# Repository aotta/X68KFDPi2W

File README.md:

# X68KFDPi2W
X68KFDPi2W - Floppies drive emulator All-In-One for Sharp X68000

The design is an evolution of my previous X68KFDPico, and allows the two drives of the X68000 to be emulated both externally and internally connected. The engine of the emulator are two Raspberry Pico, one ‘normal’ to handle the special floppy signals and the other ‘W’ to emulate the floppies, SDcard image management and a simple web server to choose the disks to be inserted in the floppies.
Ejection and insertion of the disks can be done via the two keys in the X68KFDPi2W or by connecting the cables of the original floppy keys (in case they are not present internally). The same for the internal LEDs, which are however replicated in the emulator (only the green one, the red LED is managed only for the internal one).
Floppies images format supported:

| Format | Extension | Read | Write | Notes |
|---|---|---|---|---|
| Raw sector image | `.HDM`, `.XDF` | yes | yes | X68000 2HD 1232KB (77x2x8x1024); 2HC 1.2MB (80x2x15x512) also recognised by size |
| D88 | `.D88`, `.D68`, `.88D` | yes | yes | 2HD media, any sector layout (sector sizes, numbering, deleted data). The write protect flag of the image is honoured |
| DIM (DIFC.X) | `.DIM` | yes | yes | 2HD, 2HS, 2HC, 2HDE, 26x256. 2HQ (1.44MB) is not supported (needs a 300rpm drive) |
| HFE | `.HFE` | yes | no | the drive reports write protect |

Writing to floppy images is supported: the X68000 can copy files, format disks (FORMAT) and save games to the images on the SD card.
2D/2DD (double density) images and FM sectors are not supported.

### How writing works

- WRDATA is captured by a PIO state machine that measures the time between flux transitions, and a DMA channel stores them in RAM, so no write is missed while the Pico is busy (WiFi, web server).
- Core 1, which generates the read flux, watches WRGATE and records drive, side, track and the position on the track where each write starts. A normal sector write has no ID field, so the sector is found from that position; when formatting, the ID fields written by the X68000 are used.
- Core 0 decodes the MFM data with the routines of the Adafruit Floppy library (`mfm_impl.h`), checks the CRC, updates the track in memory (a verify read returns the new data immediately) and saves the sectors to the SD card when the write session ends (step, side or drive change, or 100ms without writes).
- Track format: a whole track is longer than the capture buffer, so the sectors not captured are filled with the same fill byte used by the X68000 (log line `format: 5 sectors decoded, 3 filled with E5`).
- The serial log shows one `WR:` line per write and per save.

### Web interface

- Live status of the two drives (activity/write LED, track, R/W or read only, image format), updated every second.
- One click insert in drive 0 or 1 for every image in the folder; folders are listed first.
- "Make default" stores the full path of the image in `wifi.cfg`; on an empty drive it makes the drive start empty at power on (★ DEFAULT tag).
- "New disk": creates a blank, unformatted 2HD 1232KB image (`.HDM` or `.D88`) in the current folder; insert it and format it on the X68000 with FORMAT.

### Options (top of X68KFDPi2W.ino)

- `DEBUG_BUS` (default 0): 1 prints MOTOR / DRIVE SELECT changes on the serial port (verbose).
- `RESET_ON_DESELECT` (default 1): the head goes back to track 0 when the drive is deselected or the motor stops. Needed by games that ask to swap disks (e.g. A-JAX).
- `BUS_ON_INSERTED` (default 0): READY and the bus outputs (74LVC245) are active only while an emulated drive is in use (motor on and drive selected), as in the 03/2025 release. With 1 they follow the disk inserted signals, and some games (e.g. Dracula) hang after loading Human68k.
- `READY_FOLLOWS_MOTOR`, `DF_EN_PULLDOWN`, `TRK0_FOLLOWS_SELECT` (default 0): experimental behaviours, off.
- `READY_PULSE_ON_INSERT` (default 1): when a disk is inserted (button), READY goes low for `READY_PULSE_MS` (50 ms). The FDC sees a READY change, as with a real drive; needed by games that wait for the new disk after an eject (e.g. Valis II).

### Eject / insert controller (X68kfdPico1_11, plain Pico)

The second Pico handles the X68000 OPTION_SEL protocol (eject, lock, LED blink, disk in drive, interrupt). Version 1.10:

- The protocol runs on core 1 in a tight loop and answers an OPTION_SEL access in about 0.2 µs; buttons, LEDs and the serial log run on core 0.
- /DISK_IN_DRIVE reports the drive addressed by the last OPTION_SEL and goes HIGH (no disk) as soon as a drive that is not ours is addressed (before, drives 2/3 looked inserted).
- /INT is asserted at every disk change (eject by the X68000, button) and cleared by the next access to that drive; if it is not served it is pulsed again every 100 ms.
- The eject is ignored when the lock signal is active in the same access; buttons count only when held 30 ms.
- Options at the top of the sketch: `FORCE_DRIVE01` (1 = always drives 0/1, 0 = read the INTEXT jumper), `DIAG` (1 = print the OPTION_SEL accesses every second), `EJECT_DELAY_MS`, `INT_REPEAT_MS`, `INT_GAP_US`, `BUTTON_MS`.
- Board: "Raspberry Pi Pico".

Valis II (original Japanese version): after the intro the game ejects disk A and waits, without any message, for the next disk (Disk D) in drive 0. Load it in drive 0 from the web page and press the insert button of drive 0.

### Building the firmware

- Arduino IDE with the Raspberry Pi Pico core by Earle Philhower (tested with 6.3.x), board "Raspberry Pi Pico W".
- Libraries: Adafruit Floppy (and its dependency Adafruit BusIO); SdFat is the one included with the core.
- `drive.pio.h` is generated from `drive.pio` with `pioasm drive.pio drive.pio.h` (the Arduino IDE does not do it).
- `logo.h` contains the web page logo (from `vari/logo.png`).

A special thanks to Adafruit team for their great "Floppy library", from wich i starded for floppy emulation part.

**NOTE** Last revision fix a conflicts found when using both an internal and an external X68KFDPi2W for 4 floppy emulation, now disabled 74LVC245 when drives not enabled. 
Please use last PCB, X68KFDPico.u2f and X68KFDPi2W.u2f version!!

**NOTE 2** Some games need tricks to properly boot, for example A-JAX works when starting with both drive off (leds off). When using 2HDboot.x for launching games from HD, you must "insert" floppy 1 & 2 pushing buttons when 2hdboot starts, then "eject" pushing again button after few seconds.

You need to add a "wifi.cfg" in root of your SDcard, with this 4 text row:
SSID
WIFI PASSWORD
Default floppy in drive 0
Default floppy in drive 1

The 2 lines related to the default floppys can be omitted and changed everytime via Web server (a full path, e.g. `/games/boot.hdm`, or an empty line for an empty drive).

Gerbers file are provided for the PCB, add you pico clone, and flash the firmware ".uf2" in the Pico and in the Pico W by connecting it while pressing button on Pico and drop it in the opened windows on PC.

For any comments or questions about the projects, please use the official thread in the forum: https://nfggames.com/forum2/index.php?topic=7512.0

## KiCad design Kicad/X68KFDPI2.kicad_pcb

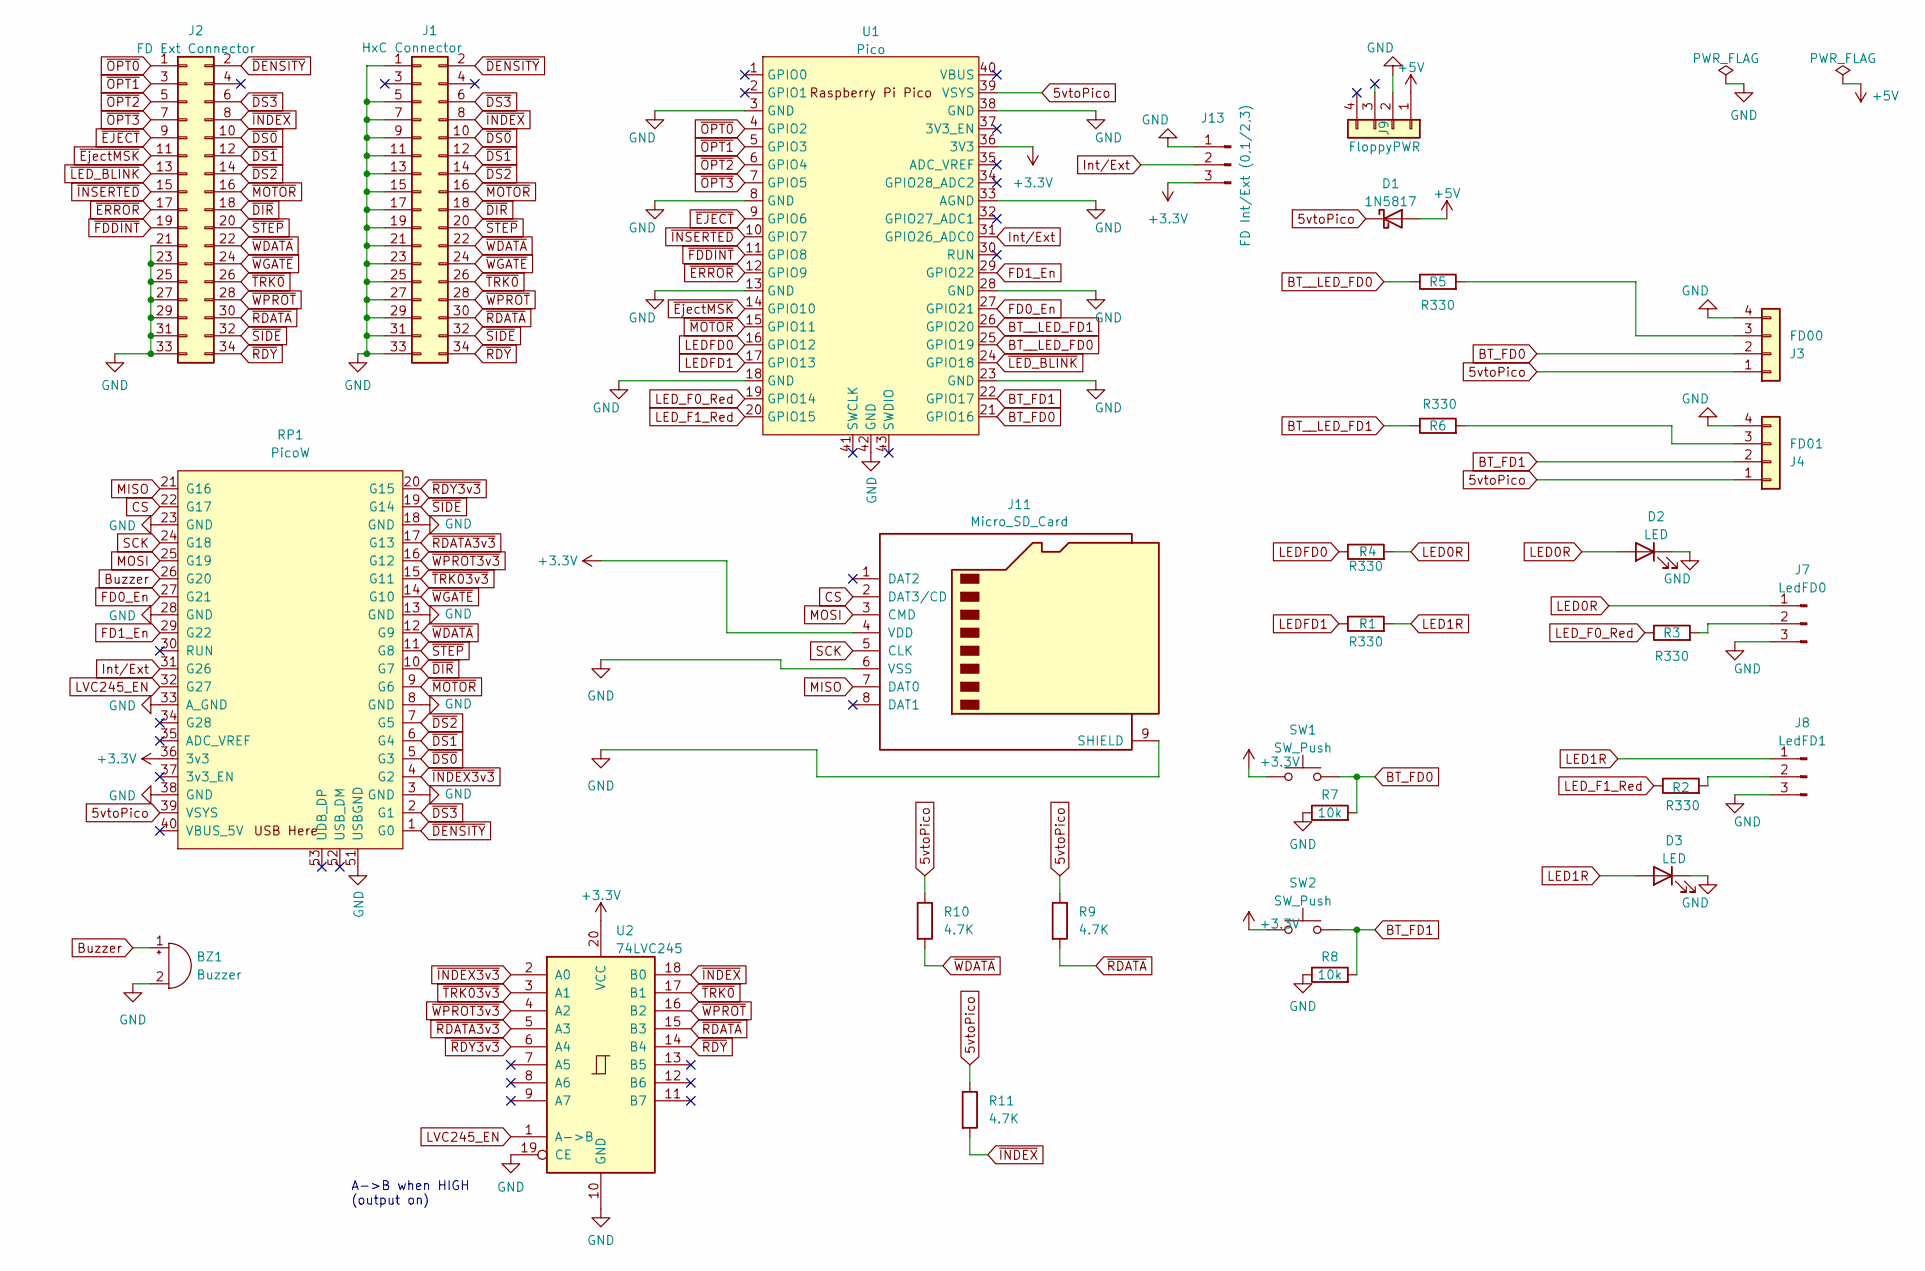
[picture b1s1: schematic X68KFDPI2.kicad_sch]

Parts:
BZ1: Buzzer; Buzzer_12x9.5RM7.6
D1: 1N5817; D_DO-15_P12.70mm_Horizontal
D2, D3: LED; LED_D3.0mm
J1: HxC Connector; IDC-Header_2x17_P2.54mm_Horizontal
J2: FD Ext Connector; IDC-Header_2x17_P2.54mm_Horizontal
J3: FD00; JST_PH_B4B-PH-K_1x04_P2.00mm_Vertical
J4: FD01; JST_PH_B4B-PH-K_1x04_P2.00mm_Vertical
J7: LedFD0; JST_PH_B3B-PH-K_1x03_P2.00mm_Vertical
J8: LedFD1; JST_PH_B3B-PH-K_1x03_P2.00mm_Vertical
J9: FloppyPWR; PinHeader_1x04_P2.54mm_Horizontal
J11: Micro_SD_Card; J_SD_Card-micro_socket_A
J13: FD Int/Ext (0,1/2,3); PinHeader_1x03_P2.54mm_Vertical
R1, R2, R3, R4, R5, R6: R330; R_Axial_DIN0207_L6.3mm_D2.5mm_P10.16mm_Horizontal
R7, R8: 10k; R_Axial_DIN0207_L6.3mm_D2.5mm_P7.62mm_Horizontal
R9, R10, R11: 4.7K; R_Axial_DIN0207_L6.3mm_D2.5mm_P7.62mm_Horizontal
RP1: PicoW; Raspberry_Pi_PicoW_SMT_THT
SW1, SW2: SW_Push; SW_Tactile_SPST_Angled_PTS645Vx83-2LFS
U1: Pico; Raspberry_Pi_PicoW_SMT_THT
U2: 74LVC245; DIP-20_W7.62mm_Socket

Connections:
5vtoPico: D1.1 (K), J3.1, J4.1, R9.1, R10.1, R11.1, RP1.39 (VSYS), U1.39 (VSYS)
+3.3V: J11.4 (VDD), J13.3, RP1.36 (3v3), SW1.1, SW2.1, U1.36 (3V3), U2.20 (VCC)
+5V: D1.2 (A), J9.1
BT_FD0: J3.2, R7.2, SW1.2, U1.21 (GPIO16)
BT_FD1: J4.2, R8.2, SW2.2, U1.22 (GPIO17)
BT__LED_FD0: R5.1, U1.25 (GPIO19)
BT__LED_FD1: R6.1, U1.26 (GPIO20)
Buzzer: BZ1.1 (+), RP1.26 (G20)
CS: J11.2 (DAT3/CD), RP1.22 (G17)
FD0_En: RP1.27 (G21), U1.27 (GPIO21)
FD1_En: RP1.29 (G22), U1.29 (GPIO22)
GND: BZ1.2 (-), D2.1 (K), D3.1 (K), J1.1, J1.5, J1.7, J1.9, J1.11, J1.13, J1.15, J1.17, J1.19, J1.21, J1.23, J1.25, J1.27, J1.29, J1.31, J1.33, J2.21, J2.23, J2.25, J2.27, J2.29, J2.31, J2.33, J3.4, J4.4, J7.3, J8.3, J9.2, J11.6 (VSS), J11.9 (SHIELD), J13.1, R7.1, R8.1, RP1.3 (GND), RP1.8 (GND), RP1.13 (GND), RP1.18 (GND), RP1.23 (GND), RP1.28 (GND), RP1.33 (A_GND), RP1.38 (GND), RP1.51 (USBGND), U1.3 (GND), U1.8 (GND), U1.13 (GND), U1.18 (GND), U1.23 (GND), U1.28 (GND), U1.33 (AGND), U1.38 (GND), U1.42 (GND), U2.10 (GND), U2.19 (CE)
Int/Ext: J13.2, RP1.31 (G26), U1.31 (GPIO26_ADC0)
LED0R: D2.2 (A), J7.1, R4.2
LED1R: D3.2 (A), J8.1, R1.2
LEDFD0: R4.1, U1.16 (GPIO12)
LEDFD1: R1.1, U1.17 (GPIO13)
LED_F0_Red: R3.1, U1.19 (GPIO14)
LED_F1_Red: R2.1, U1.20 (GPIO15)
LVC245_EN: RP1.32 (G27), U2.1 (A->B)
MISO: J11.7 (DAT0), RP1.21 (G16)
MOSI: J11.3 (CMD), RP1.25 (G19)
unnamed: J3.3, R5.2
unnamed: J4.3, R6.2
unnamed: J7.2, R3.2
unnamed: J8.2, R2.2
SCK: J11.5 (CLK), RP1.24 (G18)
~DENSITY: J1.2, J2.2, RP1.1 (G0)
~DIR: J1.18, J2.18, RP1.10 (G7)
~DS0: J1.10, J2.10, RP1.5 (G3)
~DS1: J1.12, J2.12, RP1.6 (G4)
~DS2: J1.14, J2.14, RP1.7 (G5)
~DS3: J1.6, J2.6, RP1.2 (G1)
~EJECT: J2.9, U1.9 (GPIO6)
~ERROR: J2.17, U1.12 (GPIO9)
~EjectMSK: J2.11, U1.14 (GPIO10)
~FDDINT: J2.19, U1.11 (GPIO8)
~INDEX3v3: RP1.4 (G2), U2.2 (A0)
~INDEX: J1.8, J2.8, R11.2, U2.18 (B0)
~INSERTED: J2.15, U1.10 (GPIO7)
~LED_BLINK: J2.13, U1.24 (GPIO18)
~MOTOR: J1.16, J2.16, RP1.9 (G6), U1.15 (GPIO11)
~OPT0: J2.1, U1.4 (GPIO2)
~OPT1: J2.3, U1.5 (GPIO3)
~OPT2: J2.5, U1.6 (GPIO4)
~OPT3: J2.7, U1.7 (GPIO5)
~RDATA3v3: RP1.17 (G13), U2.5 (A3)
~RDATA: J1.30, J2.30, R9.2, U2.15 (B3)
~RDY3v3: RP1.20 (G15), U2.6 (A4)
~RDY: J1.34, J2.34, U2.14 (B4)
~SIDE: J1.32, J2.32, RP1.19 (G14)
~STEP: J1.20, J2.20, RP1.11 (G8)
~TRK0: J1.26, J2.26, U2.17 (B1)
~TRK03v3: RP1.15 (G11), U2.3 (A1)
~WDATA: J1.22, J2.22, R10.2, RP1.12 (G9)
~WGATE: J1.24, J2.24, RP1.14 (G10)
~WPROT3v3: RP1.16 (G12), U2.4 (A2)
~WPROT: J1.28, J2.28, U2.16 (B2)

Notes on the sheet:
A->B when HIGH (output on)

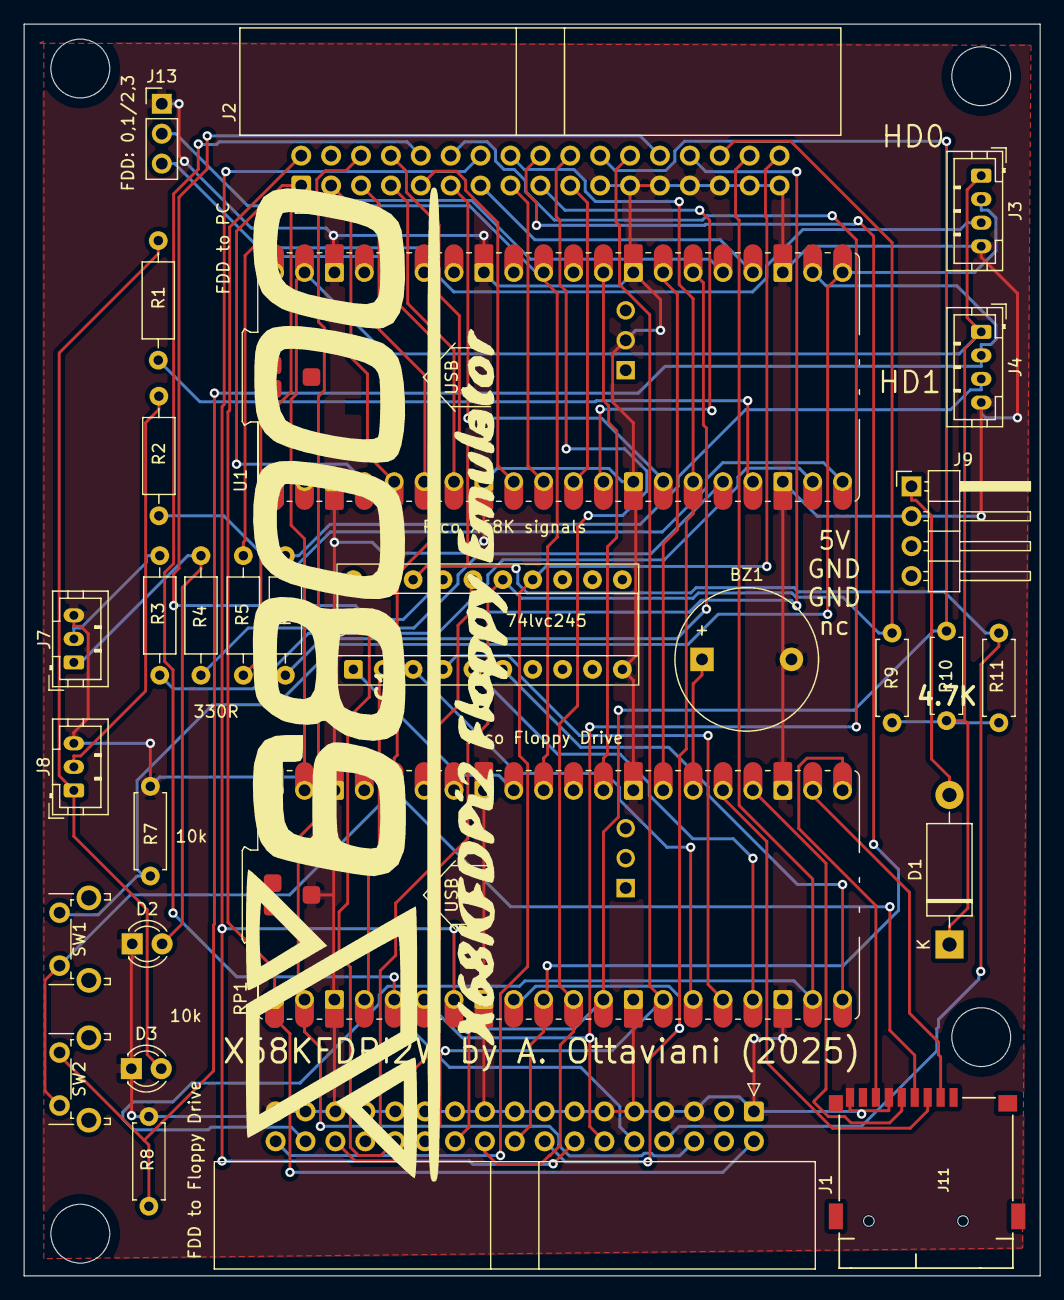
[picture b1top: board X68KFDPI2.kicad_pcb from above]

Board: 2 copper layers, 86.3 x 106.4 mm, 31 parts (1 on the bottom side), 58 nets.

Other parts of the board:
G1: LOGO; X68Klogo
Gback: LOGO; X68Klogo

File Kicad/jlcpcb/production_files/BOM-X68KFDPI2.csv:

Comment,Designator,Footprint,LCSC,Quantity
Pico,U1,Raspberry_Pi_PicoW_SMT_THT,,1
PicoW,RP1,Raspberry_Pi_PicoW_SMT_THT,,1
LedFD0,J7,JST_PH_B3B-PH-K_1x03_P2.00mm_Vertical,,1
R330,R2,R_Axial_DIN0207_L6.3mm_D2.5mm_P10.16mm_Horizontal,,1
10k,R7,R_Axial_DIN0207_L6.3mm_D2.5mm_P7.62mm_Horizontal,,1
R330,R5,R_Axial_DIN0207_L6.3mm_D2.5mm_P10.16mm_Horizontal,,1
FD01,J4,JST_PH_B4B-PH-K_1x04_P2.00mm_Vertical,,1
FloppyPWR,J9,PinHeader_1x04_P2.54mm_Horizontal,,1
R330,R1,R_Axial_DIN0207_L6.3mm_D2.5mm_P10.16mm_Horizontal,,1
74LVC245,U2,DIP-20_W7.62mm_Socket,,1
10k,R8,R_Axial_DIN0207_L6.3mm_D2.5mm_P7.62mm_Horizontal,,1
R330,R4,R_Axial_DIN0207_L6.3mm_D2.5mm_P10.16mm_Horizontal,,1
R330,R3,R_Axial_DIN0207_L6.3mm_D2.5mm_P10.16mm_Horizontal,,1
4.7K,R9,R_Axial_DIN0207_L6.3mm_D2.5mm_P7.62mm_Horizontal,,1
HxC Connector,J1,IDC-Header_2x17_P2.54mm_Horizontal,,1
4.7K,R10,R_Axial_DIN0207_L6.3mm_D2.5mm_P7.62mm_Horizontal,,1
4.7K,R11,R_Axial_DIN0207_L6.3mm_D2.5mm_P7.62mm_Horizontal,,1
"FD Int/Ext (0,1/2,3)",J13,PinHeader_1x03_P2.54mm_Vertical,,1
LED,D3,LED_D3.0mm,,1
1N5817,D1,D_DO-15_P12.70mm_Horizontal,,1
FD Ext Connector,J2,IDC-Header_2x17_P2.54mm_Horizontal,,1
SW_Push,SW1,SW_Tactile_SPST_Angled_PTS645Vx83-2LFS,,1
LedFD1,J8,JST_PH_B3B-PH-K_1x03_P2.00mm_Vertical,,1
Buzzer,BZ1,Buzzer_12x9.5RM7.6,,1
Micro_SD_Card,J11,J_SD_Card-micro_socket_A,,1
SW_Push,SW2,SW_Tactile_SPST_Angled_PTS645Vx83-2LFS,,1
FD00,J3,JST_PH_B4B-PH-K_1x04_P2.00mm_Vertical,,1
LED,D2,LED_D3.0mm,,1
R330,R6,R_Axial_DIN0207_L6.3mm_D2.5mm_P10.16mm_Horizontal,,1

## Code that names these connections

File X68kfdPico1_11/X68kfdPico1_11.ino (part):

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// 1 = always drives 0/1 (ignore the INTEXT jumper), 0 = read the jumper
// Like a real drive: after the eject command the disk takes a while to leave
// the drive, then /INT is asserted until the next access to that drive.
#define EJECT_DELAY_MS 0   // 0 = "no disk" right after the eject command (A-Jax checks it at once)
#define INT_MIN_MS 0      // 0 = cleared by the first access, like a real drive
#define INT_REPEAT_MS 100  // /INT not served: new falling edge every INT_REPEAT_MS
#define INT_GAP_US 200     // ... after releasing the line for INT_GAP_US
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#define FORCE_DRIVE01 0

//Cablage
#define OPT0                2  // Set D2 as OPT0 Read strobe
#define OPT1                3  // Set D3 as OPT1 Read strobe
#define OPT2                4  // Set D4 as OPT2 Read strobe
#define OPT3                5  // Set D5 as OPT3 Read strobe
#define Eject               6  // Set D6 as Eject Read strobe
#define Inserted            7  // Set D7 as Inserted Read strobe
#define FDDINT              8  // Set D8 as FD Interrupt Read strobe
#define Error               9  // Set D9 as Error Read strobe
#define EjectMSK           10  // Set D10 as EjectMSK Read strobe
#define Motor              11  // Set D11 as Motor Read strobe
#define LEDFD0             12  // Set D12 as LED FD0 output (Green LED)
#define LEDFD1             13  // Set D13 as LED FD1 output (Green LED)
#define LED_FD0_RED        14  // Set D14 as LED FD0 output (Red LED)
#define LED_FD1_RED        15  // Set D15 as LED FD1 output (Red LED)
#define BT_FD0             16  // Set D16 as Button FD0 Read strobe
#define BT_FD1             17  // Set D17 as Button FD1 Read strobe
#define LED_BLINK          18  // Set A0 as LED (Blink) output
#define BT_FD0_INT         19  // Set D19 as Button FD0 Read strobe from internal floppy
#define BT_FD1_INT         20  // Set D20 as Button FD1 Read strobe from internal floppy
#define DF0_EN             21  // "disk in drive 0" to the Pico W
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uint optPin[2];

void setup() {
  pinMode(OPT0, INPUT_PULLUP);
  pinMode(OPT1, INPUT_PULLUP);
  pinMode(OPT2, INPUT_PULLUP);
  pinMode(OPT3, INPUT_PULLUP);
  pinMode(Eject, INPUT_PULLUP);
  pinMode(BT_FD0, INPUT);
  pinMode(BT_FD1, INPUT);
  pinMode(LED_BLINK, INPUT_PULLUP); // Blink
  pinMode(EjectMSK, INPUT_PULLUP);  // LOCK
  pinMode(Motor, INPUT_PULLUP);
  digitalWrite(Inserted, HIGH); pinMode(Inserted, OUTPUT);
  digitalWrite(Error, HIGH);    pinMode(Error, OUTPUT);
  digitalWrite(FDDINT, HIGH);   pinMode(FDDINT, OUTPUT);
  pinMode(LEDFD0, OUTPUT);
  pinMode(LEDFD1, OUTPUT);
  pinMode(LED_FD0_RED, OUTPUT);
  pinMode(LED_FD1_RED, OUTPUT);
  pinMode(BT_FD0_INT, OUTPUT);
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#else
  bool d01 = digitalRead(INTEXT);
#endif
  optPin[0] = d01 ? OPT0 : OPT2;
  optPin[1] = d01 ? OPT1 : OPT3;
  core1_ready = true;
}

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
void __attribute__((optimize("O2"))) __not_in_flash_func(loop1)() {
  const uint32_t mA = 1u << optPin[0], mB = 1u << optPin[1];
  const uint32_t mOpt = (1u << OPT0) | (1u << OPT1) | (1u << OPT2) | (1u << OPT3);
  const uint32_t mOther = mOpt & ~(mA | mB);
  const uint32_t mEj = 1u << Eject, mLk = 1u << EjectMSK, mBl = 1u << LED_BLINK;
  const uint32_t mIns = 1u << Inserted, mInt = 1u << FDDINT;
  int who = -1;                       // drive addressed by the last strobe, -1 = not ours
  bool d[2] = {disk[0], disk[1]};
  bool intp[2] = {false, false};      // interrupt pending per drive
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  static bool prev_disk[2] = {false, false}, prev_lock[2] = {false, false}, prev_blink[2] = {false, false};
  static uint32_t prev_ej[2] = {0, 0};
  static bool started = false;
  const int btn[2] = {BT_FD0, BT_FD1};
  const int green[2] = {LEDFD0, LEDFD1}, red[2] = {LED_FD0_RED, LED_FD1_RED};
  const int intout[2] = {BT_FD0_INT, BT_FD1_INT}, en[2] = {DF0_EN, DF1_EN};
  uint32_t now = millis();

  if (!started && now > 2000) {
    started = true;
    Serial.printf("X68kfdPico1 v1.10 - drives %s\n", optPin[0] == OPT0 ? "0/1" : "2/3");
  }

#if DIAG
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  bool blink_phase = (now / 250) & 1;

  for (int k = 0; k < 2; k++) {
    int n = (optPin[0] == OPT0 ? 0 : 2) + k;
    // debounce: the press counts once, after BUTTON_MS held, and the button
    // must be released before the next one (filters glitches, e.g. plugging USB)
    static uint32_t down_since[2] = {0, 0};
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
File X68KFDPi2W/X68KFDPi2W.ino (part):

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
// Experiments of 01/2026 ("poivia"), off = behaviour of the 03/2025 release.
// With both at 1 Dracula hangs after loading Human68k.
#define READY_FOLLOWS_MOTOR 0 // 1 = READY = !motor at every loop
#define DF_EN_PULLDOWN 0      // 1 = pull-down on the DF0_EN/DF1_EN inputs
#define BUS_ON_INSERTED 0     // 1 = READY and bus outputs (74LVC245) on while a
                              // disk is inserted (DF0_EN/DF1_EN); 0 = only while
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#include <LEAmDNS.h>
#include <StreamString.h>

#define DENSITY_PIN    0  // IDC 2
#define SELECT_PIN3    1  // IDC 6  DRIVE SELECT DS3
#define INDEX_PIN      2  // IDC 8   // output from PicoFloppy
#define SELECT_PIN0    3  // IDC 10 DRIVE SELECT DS0
#define SELECT_PIN1    4  // IDC 12 DRIVE SELECT DS1
#define SELECT_PIN2    5  // IDC 14 DRIVE SELECT DS2
#define MOTOR_PIN      6  // IDC 16
#define DIR_PIN        7  // IDC 18
#define STEP_PIN       8  // IDC 20
#define WRDATA_PIN     9  // IDC 22 //input for reading from PC when writing SD
#define WRGATE_PIN    10  // IDC 24 // input for writing on disk
#define TRK0_PIN      11  // IDC 26 // output from PicoFloppy
#define PROT_PIN      12  // IDC 28 // output from PicoFloppy
#define READ_PIN      13  // IDC 30 // output from PicoFloppy
#define SIDE_PIN      14  // IDC 32
#define READY_PIN     15  // IDC 34  // output from PicoFloppy
#define BUZZER_PIN    20  // Output pin for sound
#define DF0_EN        21  // Info for drive A enabled from other PICO
#define DF1_EN        22  // Info for drive B enabled from other PICO
#define INTEXT        26  // Read from jumper - FD0-1 when HIGH, FD2-3 when LOW
#define LVC245_EN     27  // Enable output to FD bus when HIGH


char ssid[40];
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    else if (!gpio_get(SELECT_PINB))
      drive = 1;
    seg->drive = drive;
    seg->side = !gpio_get(SIDE_PIN);
    seg->track = (drive == 1) ? trackno1 : trackno0;
    seg->pos = (drive >= 0 && drive == out_drive && seg->side == out_side)
                   ? out_pos
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void onStep() {
  
  if ((!digitalRead(SELECT_PINB))) {
    auto enabled1 = !digitalRead(SELECT_PINB); // motor need not be enabled to seek tracks
    auto direction = digitalRead(DIR_PIN);
    int new_track1 = trackno1;
    if (direction) {
      if (new_track1 > 0)
        new_track1--;
        tone(BUZZER_PIN, NOTE_G4, 250);
        noTone(BUZZER_PIN);
    } else {
    if (new_track1 < max_track[1])
      new_track1++;
      tone(BUZZER_PIN, NOTE_F7, 250);
      noTone(BUZZER_PIN);
    }
    if (enabled1) {
    trackno1 = new_track1;
    digitalWrite(TRK0_PIN, trackno1 != 0); // active LOW
    }
  }
  
  
  if ((!digitalRead(SELECT_PINA))) {
    auto enabled0 =  !digitalRead(SELECT_PINA); // motor need not be enabled to seek tracks
    auto direction = digitalRead(DIR_PIN);
    int new_track0 = trackno0;
    if (direction) {
      if (new_track0 > 0)
        new_track0--;
        tone(BUZZER_PIN, NOTE_G4, 250);
        noTone(BUZZER_PIN);
    } else {
      if (new_track0 < max_track[0])
      new_track0++;
      tone(BUZZER_PIN, NOTE_F7, 250);
      noTone(BUZZER_PIN);
    }
    if (enabled0) {
      trackno0 = new_track0;
      digitalWrite(TRK0_PIN, trackno0 != 0); // active LOW
    }
  }
  
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
// Funzione per leggere una riga da un file
int readRiga(File32 &file, char *buffer, size_t bufferSize) {
  int index = 0;
  int byteRead;
  memset(buffer,0,sizeof(buffer));

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
  offset_index_pulse = pio_add_program(pio, &index_pulse_program);
  sm_index_pulse = pio_claim_unused_sm(pio, true);
  index_pulse_program_init(pio, sm_index_pulse, offset_index_pulse, INDEX_PIN,
                           1000);
  
  pinMode(DIR_PIN, INPUT_PULLUP);
  pinMode(STEP_PIN, INPUT_PULLUP);
  pinMode(SIDE_PIN, INPUT_PULLUP);
  pinMode(MOTOR_PIN, INPUT_PULLUP);
  pinMode(SELECT_PIN0, INPUT_PULLUP);
  pinMode(SELECT_PIN1, INPUT_PULLUP);
  pinMode(SELECT_PIN2, INPUT_PULLUP);
  pinMode(SELECT_PIN3, INPUT_PULLUP);
  pinMode(WRGATE_PIN, INPUT_PULLUP);
  //pinMode(WRDATA_PIN, INPUT_PULLUP);
  pinMode(TRK0_PIN, OUTPUT);
  pinMode(READY_PIN, OUTPUT);
  pinMode(PROT_PIN, OUTPUT);  
  digitalWrite(READY_PIN, HIGH); // active low
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  pinMode(DF1_EN, INPUT);
#endif
  pinMode(INTEXT,INPUT_PULLUP);
  pinMode(LVC245_EN,OUTPUT);
  digitalWrite(LVC245_EN, HIGH); // Output when HIGH
 
  
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void loop() {
  auto new_trackno0 = trackno0;
  auto new_trackno1 = trackno1;
  int motor_pin = !digitalRead(MOTOR_PIN);
  int select_pin0 = !digitalRead(SELECT_PINA);
  int select_pin1 = !digitalRead(SELECT_PINB);
  int inserted0 = digitalRead(DF0_EN);
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  rp_prev0 = inserted0; rp_prev1 = inserted1;
  if (ready_pulse_until && (int32_t)(millis() - ready_pulse_until) >= 0) ready_pulse_until = 0;
#endif
  int side = !digitalRead(SIDE_PIN);
  
  //Serial.println(inserted0);
  
  auto enabled0 = (motor_pin && select_pin0);  
  auto enabled1 = (motor_pin && select_pin1);
  if (!filename0[0] || img_err0) enabled0=0;
  if (!filename1[0] || img_err1) enabled1=0;

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
  // Write protect of the selected drive (active LOW)
  bool wprot = false;
  if (select_pin0 && filename0[0]) wprot = !wr_allowed0;
  else if (select_pin1 && filename1[0]) wprot = !wr_allowed1;
  digitalWrite(PROT_PIN, wprot ? LOW : HIGH);

#if TRK0_FOLLOWS_SELECT
  // TRACK 0 of the selected drive (active LOW): each drive has its own head
  if (select_pin0) digitalWrite(TRK0_PIN, trackno0 != 0);
  else if (select_pin1) digitalWrite(TRK0_PIN, trackno1 != 0);
#endif
    
   //auto enabled = true;
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  static bool old_inserted0 = false, old_inserted1 = false;
#if DEBUG_BUS
  static int old_bus = -1;
  int bus = motor_pin | (select_pin0 << 1) | (select_pin1 << 2);
  if (bus != old_bus) {
    Serial.printf("BUS: motor=%d sel0=%d sel1=%d trk=%d/%d\n", motor_pin, select_pin0,
                  select_pin1, trackno0, trackno1);
    old_bus = bus;
  }
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  // on the "ready / disk change:
  
#if READY_FOLLOWS_MOTOR
  digitalWrite(READY_PIN, !motor_pin); //poivia
#endif
   
#if READY_PULSE_ON_INSERT
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
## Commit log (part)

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2025-03-03 Added 74lvc245 dir control
    Test in progress for avoiding conflict when 2 x68kfdpi2w are used togheter
2025-03-03 fixed 4 drive support with 2 X68KFDPi2W
    fixed 4 drive support with 2 X68KFDPi2W (last pcb version required)
2025-03-03 Fixed
2025-03-03 Add files via upload
    fix
2025-03-05 Add files via upload
    last test version
2025-03-05 Add files via upload
    fix for internal red led
2025-03-05 last fix
2025-03-10 Fix for drive 0/1-2/3
2025-03-10 Add files via upload
    fix+moved button connectors
2025-03-10 fix+moved button connectors
2025-03-10 Fix - version with drive number from switch
2025-03-19 fix issue with 2hdboot.x
2025-03-19 Update README.md
    added note for 2hdboot.x
2026-05-09 Fixed 5vsb power to gnd in power connector
2026-05-09 Fixed fdd power connector
    Fixed 5vsb to gnd in fdd power connector for some models

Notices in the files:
parts and their libraries:
This public domain footprint does not match the original source as it has been modified to better fit this application
